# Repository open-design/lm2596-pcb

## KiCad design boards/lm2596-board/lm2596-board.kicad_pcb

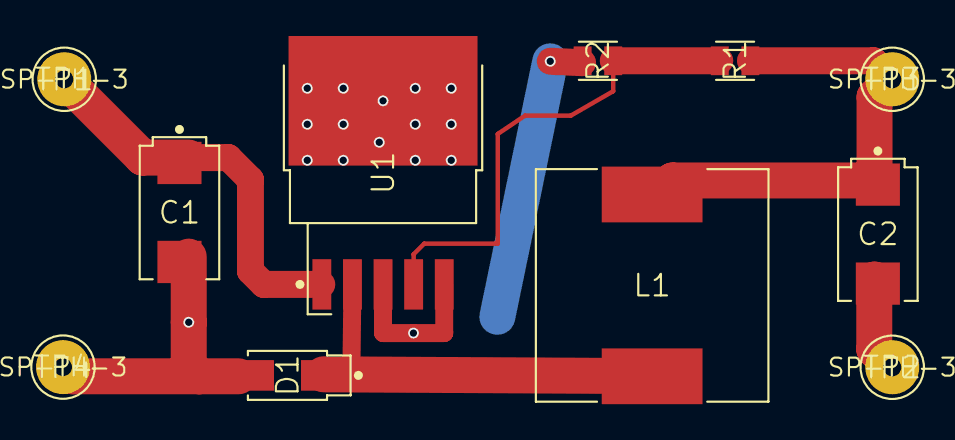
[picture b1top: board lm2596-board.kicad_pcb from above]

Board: 2 copper layers, 11 parts (0 on the bottom side), 5 nets.

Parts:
C1: 100 uF, 50V; CAPPM7343X310N
C2: 220 uF, 35 V; CAPPM7343X310N
D1: B340A; DIOM4326X290N
L1: B82477G4; INDM128128X800N
R1: 15.4k; RESC2013X65N
R2: 1k; RESC2013X65N
TP1, TP2, TP3, TP4: SP-TH-3
U1: LM2596S; TO170P1023X864X465-5N

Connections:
/GND: C1.2, C2.2, D1.2, R2.1, TP2.1, TP4.1, U1.3, U1.5, U1.6
/IN+: C1.1, TP1.1, U1.1
/OUT+: C2.1, L1.2, R1.2, TP3.1
unnamed: D1.1, L1.1, U1.2
unnamed: R1.1, R2.2, U1.4

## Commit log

2017-11-12 boards: add lm2596-board
2017-11-12 [EPIC FAIL] library: add through hole resistors
2017-11-12 [TMP]: add generated stuff
